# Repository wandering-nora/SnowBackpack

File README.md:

# SnowBackpack
Cute ESP32-C3 backpack for 2 x n [SnowPixel](https://github.com/wandering-nora/SnowPixel) matrix displays.

This board can power a grid of 2+ SnowPixel displays without any wiring in a thin package.

The main features are:
- ESP8685H4 RISC-V mcu with 4MB of flash, Wifi and BLE @160MHz
- Battery charging for protected 1s lipo cells
- ST LSM6DSO 6-axis low power accelerometer
- Efficient 5V boost converter with 500mA max current for the SnowPixel modules
- Onboard ceramic antenna

The board has no power switch, the MCU can deep sleep and be woken up by the always on IMU with two interrupt pins. The 5V boost converter can also be switched off leaving only the 3.3V rail and IMU operational for very low static power consumption.

> Note:  for normal operation R13 and R14  are unpopulated

## Manufacturing update
After assembly with a hot plate everything works as intended ^_^  
There's only a couple of things I would change for V1.2 which should keep my stencil mostly reusable.

#### Todo for V1.2
- [ ] Get rid of jumper on data out pad
- [ ] Change battery connector to a 1A capable one
- [ ] Consider removing extra pads on long edge

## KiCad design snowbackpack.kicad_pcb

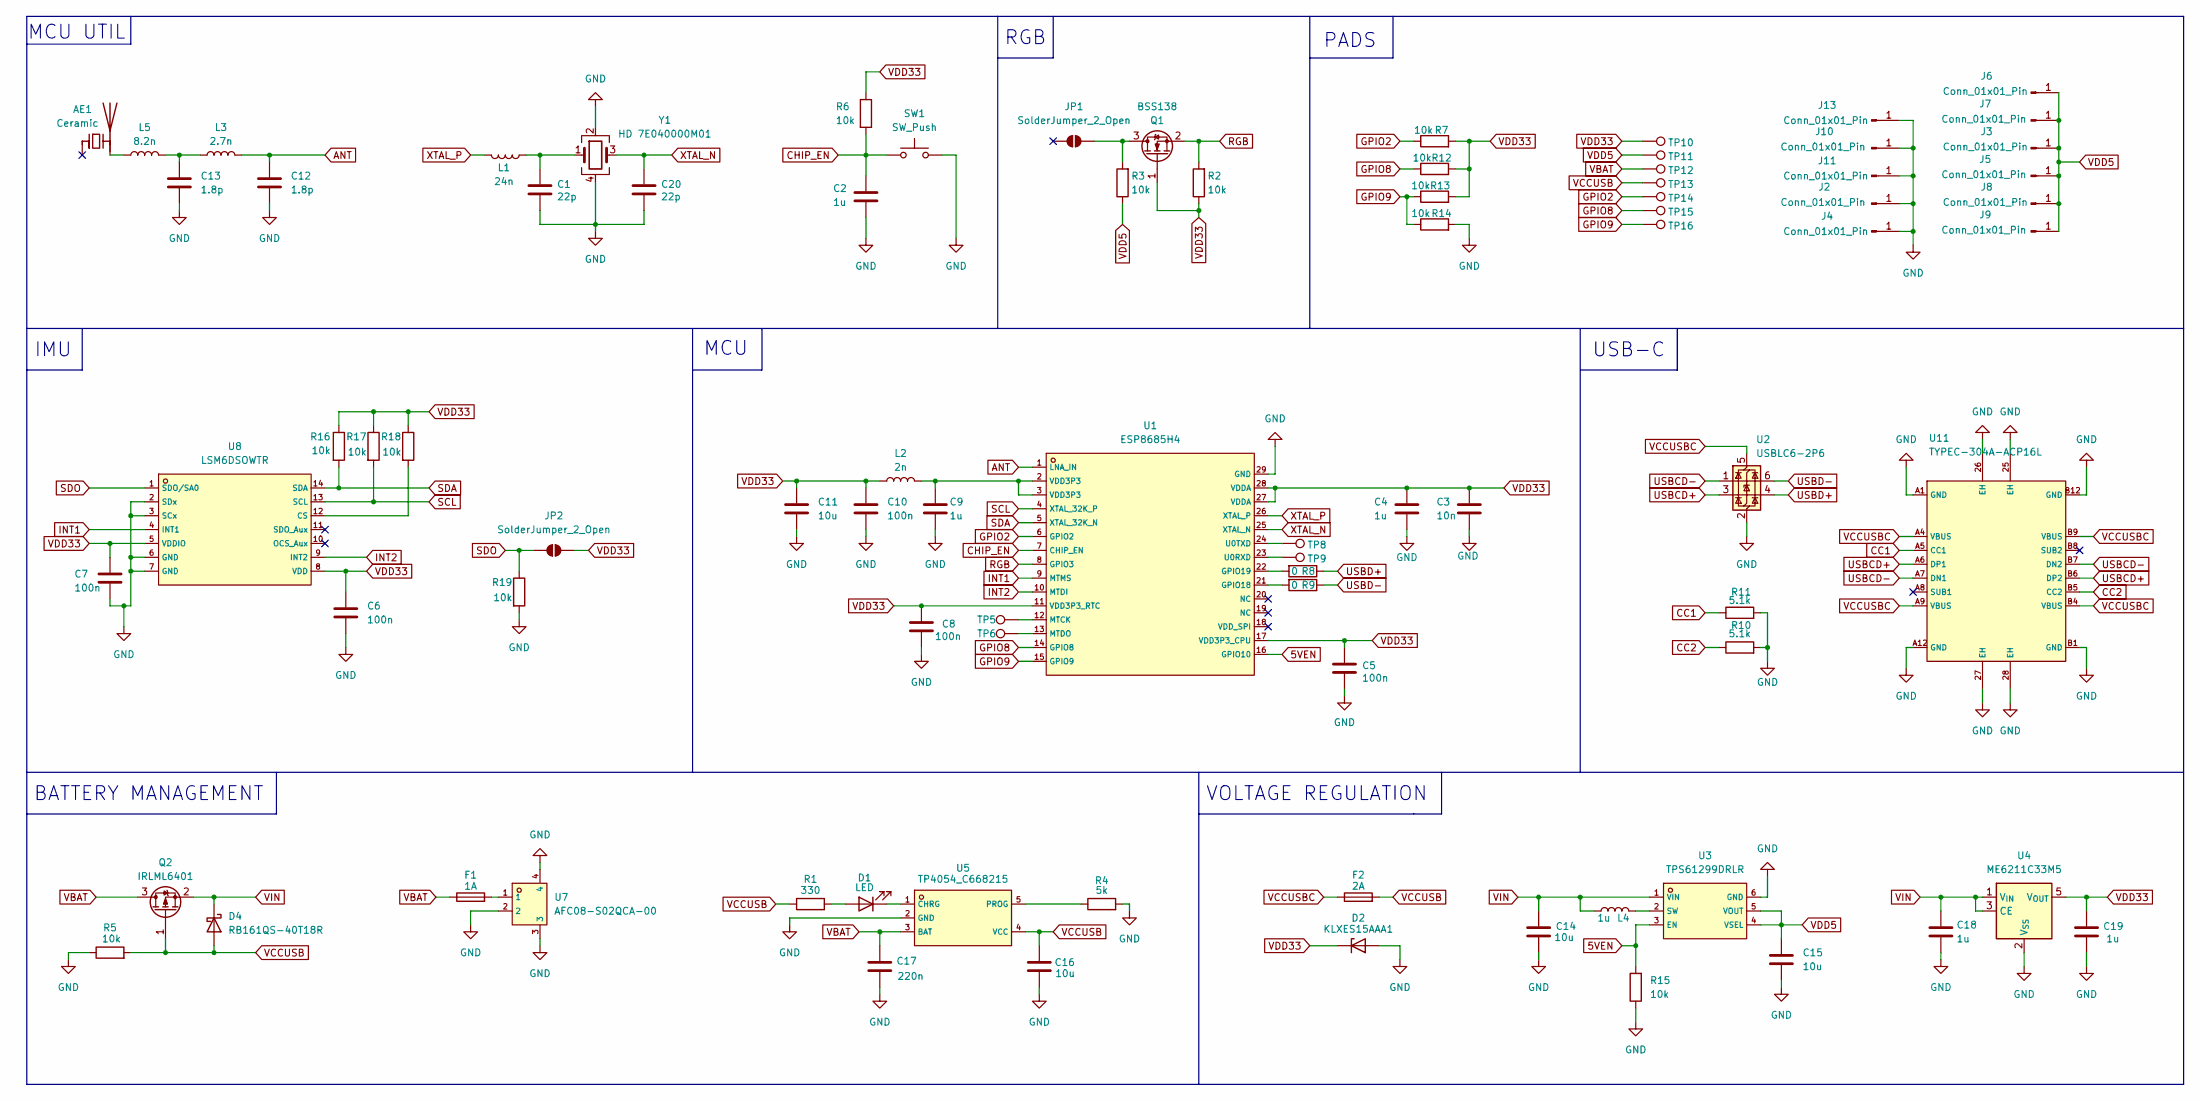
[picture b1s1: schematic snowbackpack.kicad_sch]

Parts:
AE1: Ceramic; CW324S
C1, C20: 22p; C_0402_1005Metric
C2, C4, C9, C18, C19: 1u; C_0402_1005Metric
C3: 10n; C_0402_1005Metric
C5, C6, C7, C8, C10: 100n; C_0402_1005Metric
C11, C14, C15, C16: 10u; C_0402_1005Metric
C12, C13: 1.8p; C_0402_1005Metric
C17: 220n; C_0402_1005Metric
D1: LED; LED_0603_1608Metric
D2: KLXES15AAA1; D_0402_1005Metric
D4: RB161QS-40T18R; D_0402_1005Metric
F1: 1A; Fuse_0402_1005Metric
F2: 2A; Fuse_0402_1005Metric
J2, J4, J10, J11, J13: Conn_01x01_Pin; matrix-pad-gn
J3, J5, J6, J7, J8, J9: Conn_01x01_Pin; matrix-pad-vcc
JP1: SolderJumper_2_Open; matrix-pad-dout
JP2: SolderJumper_2_Open; SolderJumper-2_P1.3mm_Open_RoundedPad1.0x1.5mm
L1: 24n; L_0402_1005Metric
L2: 2n; L_0402_1005Metric
L3: 2.7n; L_0402_1005Metric
L4: 1u; IND-SMD_L2.5-W2.0
L5: 8.2n; L_0402_1005Metric
Q1: BSS138; SOT-23
Q2: IRLML6401; SOT-23
R1: 330; R_0402_1005Metric
R2, R3, R5, R6, R7, R12, R13, R14, R15, R16, R17, R18, R19: 10k; R_0402_1005Metric
R4: 5k; R_0402_1005Metric
R8, R9: 0; R_0402_1005Metric
R10, R11: 5.1k; R_0402_1005Metric
SW1: SW_Push; KEY-SMD_B3U-1000PM
TP5, TP6, TP8, TP9, TP10, TP11, TP12, TP13, TP14, TP15, TP16: TestPoint; TestPoint_Pad_D1.0mm
U1: ESP8685H4; QFN-28_L4.0-W4.0-P0.40-TL-EP2.7; LCSC C4944062
U2: USBLC6-2P6; SOT-666
U3: TPS61299DRLR; SOT-563-6_L1.6-W1.2-P0.50-LS1.6-BL; LCSC C41689719
U4: ME6211C33M5; SOT-23-5
U5: TP4054_C668215; TSOT-23-5_L2.9-W1.6-P0.95-LS2.8-BR; LCSC C668215
U7: AFC08-S02QCA-00; CONN-SMD_2P-P0.80_JUSHUO_AFC08-S02QCA-00; LCSC C2934855
U8: LSM6DSOWTR; LGA-14L_L3.0-W2.5-P0.50-TL; LCSC C2829074
U11: TYPEC-304A-ACP16L; USB-C-SMD_XUNPU_TYPEC-304A-ACP16L; LCSC C2909609
Y1: HD 7E040000M01; CRYSTAL-SMD_4P-L1.6-W1.2-BL

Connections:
5VEN: R15.2, U1.16 (GPIO10), U3.3 (EN)
ANT: C12.2, L3.2, U1.1 (LNA_IN)
CC1: R11.1, U11.A5 (CC1)
CC2: R10.1, U11.B5 (CC2)
CHIP_EN: C2.1, R6.2, SW1.1, U1.7 (CHIP_EN)
GND: C1.2, C2.2, C3.2, C4.2, C5.1, C6.2, C7.2, C8.1, C9.2, C10.2, C11.2, C12.1, C13.1, C14.1, C15.2, C16.1, C17.1, C18.2, C19.1, C20.2, D2.2 (A), J2.1, J4.1, J10.1, J11.1, J13.1, R4.2, R5.1, R10.2, R11.2, R14.2, R15.1, R19.2, SW1.2, U1.29 (GND), U2.2 (GND), U3.6 (GND), U4.2 (V_{SS}), U5.2 (GND), U7.2, U7.3, U7.4, U8.2 (SDx), U8.3 (SCx), U8.6 (GND), U8.7 (GND), U11.25 (EH), U11.26 (EH), U11.27 (EH), U11.28 (EH), U11.A1 (GND), U11.A12 (GND), U11.B1 (GND), U11.B12 (GND), Y1.2, Y1.4
GPIO2: R7.1, TP14.1, U1.6 (GPIO2)
GPIO8: R12.1, TP15.1, U1.14 (GPIO8)
GPIO9: R13.1, R14.1, TP16.1, U1.15 (GPIO9)
INT1: U1.9 (MTMS), U8.4 (INT1)
INT2: U1.10 (MTDI), U8.9 (INT2)
unnamed: AE1.2 (PCB_Trace), L5.1
unnamed: C1.1, L1.1, Y1.1
unnamed: C9.1, L2.2, U1.2 (VDD3P3), U1.3 (VDD3P3)
unnamed: C13.2, L3.1, L5.2
unnamed: D1.2 (A), R1.2
unnamed: D1.1 (K), U5.1 (CHRG)
unnamed: F1.2, U7.1
unnamed: JP1.2 (B), Q1.3 (D), R3.2
unnamed: R9.2, U1.21 (GPIO18)
unnamed: R8.2, U1.22 (GPIO19)
unnamed: TP5.1, U1.12 (MTCK)
unnamed: TP6.1, U1.13 (MTDO)
unnamed: TP9.1, U1.23 (U0RXD)
unnamed: TP8.1, U1.24 (U0TXD)
unnamed: L4.2, U3.2 (SW)
unnamed: R4.1, U5.5 (PROG)
unnamed: R18.2, U8.12 (CS)
RGB: Q1.2 (S), R2.2, U1.8 (GPIO3)
SCL: R17.2, U1.4 (XTAL_32K_P), U8.13 (SCL)
SDA: R16.2, U1.5 (XTAL_32K_N), U8.14 (SDA)
SDO: JP2.2 (B), R19.1, U8.1 (SDO/SA0)
USBCD+: U2.3 (I/O2), U11.A6 (DP1), U11.B6 (DP2)
USBCD-: U2.1 (I/O1), U11.A7 (DN1), U11.B7 (DN2)
USBD+: R8.1, U2.4 (I/O2)
USBD-: R9.1, U2.6 (I/O1)
VBAT: C17.2, F1.1, Q2.3 (D), TP12.1, U5.3 (BAT)
VCCUSB: C16.2, D4.2 (A), F2.2, Q2.1 (G), R1.1, R5.2, TP13.1, U5.4 (VCC)
VCCUSBC: F2.1, U2.5 (VBUS), U11.A4 (VBUS), U11.A9 (VBUS), U11.B4 (VBUS), U11.B9 (VBUS)
VDD5: C15.1, J3.1, J5.1, J6.1, J7.1, J8.1, J9.1, R3.1, TP11.1, U3.4 (VSEL), U3.5 (VOUT)
VDD33: C3.1, C4.1, C5.2, C6.1, C7.1, C8.2, C10.1, C11.1, C19.2, D2.1 (K), JP2.1 (A), L2.1, Q1.1 (G), R2.1, R6.1, R7.2, R12.2, R13.2, R16.1, R17.1, R18.1, TP10.1, U1.11 (VDD3P3_RTC), U1.17 (VDD3P3_CPU), U1.27 (VDDA), U1.28 (VDDA), U4.5 (V_{OUT}), U8.5 (VDDIO), U8.8 (VDD)
VIN: C14.2, C18.1, D4.1 (K), L4.1, Q2.2 (S), U3.1 (VIN), U4.1 (V_{IN}), U4.3 (CE)
XTAL_N: C20.1, U1.25 (XTAL_N), Y1.3
XTAL_P: L1.2, U1.26 (XTAL_P)

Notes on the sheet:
IMU
VOLTAGE REGULATION
MCU UTIL
BATTERY MANAGEMENT
PADS
MCU
RGB
USB-C

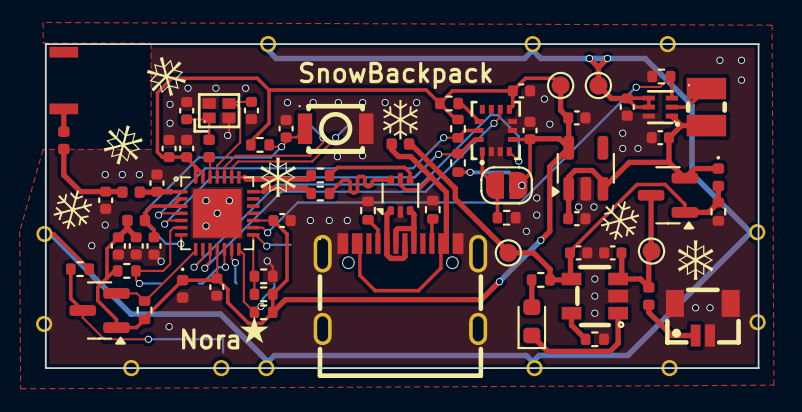
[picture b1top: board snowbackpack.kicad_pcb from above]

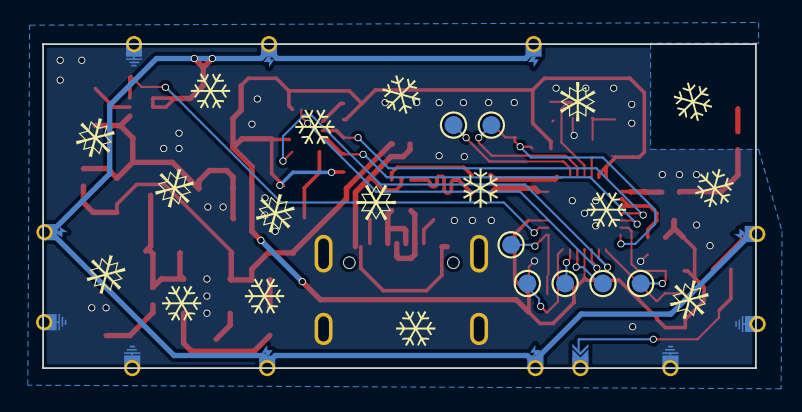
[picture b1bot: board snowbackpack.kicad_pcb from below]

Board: 2 copper layers, 39.6 x 18.0 mm, 86 parts (19 on the bottom side), 44 nets.

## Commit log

2025-03-12 First pcb routing
2025-03-12 Fixed smd antenna
2025-03-12 Routed USB
2025-03-12 Added images
2025-03-12 Update images
2025-03-12 Update pcb silkscreen
2025-03-12 Updated silkscreen with snowflakes
2025-03-12 Slightly reduce clutter on silkscreen
2025-03-13 Fixed interconnect spacing
2025-03-15 Added v1 gerber files
2025-03-17 added BOM and cleaned up schematics
2025-03-17 Updated BOM
2025-03-18 Change folder structure for release
2025-03-21 Fix image alignment in readme
2025-03-31 Fix 3d models
2025-03-31 Add render
2025-04-29 Removed unused images
2025-04-29 add license
